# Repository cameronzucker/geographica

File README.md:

<!-- HEADER -->

# Geographica

**Offline-first GIS platform for field operations on disconnected networks.** A complete mapping stack — vector basemaps, aerial imagery, terrain, routing, geocoding, GPS — running on a single Raspberry Pi 5.

<br clear="left" />

<!-- ONE-PARAGRAPH ELABORATION -->
Built for [AREDN](https://www.arednmesh.org/) mesh networks and field teams operating without cloud connectivity. Acquire data once on a connected workstation, then deploy anywhere — wilderness, disaster recovery, off-grid bases, or mesh-network coverage areas. After initial data acquisition, no internet connection is required.

<!-- HERO SCREENSHOT -->

<!-- HOW IT WAS BUILT CALLOUT -->
> **How it was built:** 19 days. One engineer plus a team of Claude agents working under structured agent-orchestration patterns — brainstorm, adversarial review, TDD execution by parallel sub-agents. Inference cost: **~$300 of API-equivalent model output**, paid as a Claude Max subscription (~$200/mo). [Read the process →](docs/PROCESS.md) · [Cost methodology →](docs/COST_METHODOLOGY.md)

## Features

<p align="center">

<br>
<em>3D hillshade terrain (above) and public lands overlay with agency-colored fills (below).</em>
</p>

### Mapping & imagery

- **Vector basemaps** — three themes (Positron light, Dark Matter dark, Hybrid imagery+roads) with house-number labels.
- **Aerial imagery** — five acquisition modes (USGS Direct, NOAA NAIP, National Map ImageServer, USGS M2M API, BYO GeoTIFF). Per-source toggles, opacity slider, dynamic basemap restyling when imagery is active.
- **Public lands layer** — BLM, National Forest, National Park, Fish & Wildlife, Military, Bureau of Reclamation, Tribal, State Trust, and Wilderness boundaries. Agency-colored fills, tribal-boundary diagonal stripes, full legend.
- **3D terrain** — hillshade overlay, adjustable exaggeration slider, free-look camera (pitch/bearing control).

<br clear="right" />

### Spatial intelligence

- **Natural-language spatial search** — "nearest gas station", "hospitals near me", "gas stations along my route", "fuel every 50 miles", "gas stations in Flagstaff", "restaurants in Phoenix along my route". Distance-ranked results, numbered map pins, city-aware geocoding.
- **Voice search** — push-to-hold mic button for hands-free queries via Whisper (base.en, CPU). Requires HTTPS.
- **OSM POI search** — commercial amenities (fuel, food, lodging, pharmacy, grocery) and public-land boundaries extracted from OSM data.
- **Geocoding** — Nominatim-backed search for addresses, cities, landmarks.
- **POI search** — GNIS gazetteer with full-text search.

<br clear="right" />

### Navigation & GPS

- **Turn-by-turn navigation** — voice guidance, off-route detection, dead reckoning.
- **Multi-stop waypoint routing** — map-click point selection for car, bicycle, and pedestrian profiles.
- **Live GPS** — hardware GPS streaming over WebSocket with accuracy circle display.
- **KML/KMZ import** — drag-and-drop file overlay with layer management panel and IndexedDB session persistence.
- **Coordinate display** — Maidenhead grid locator and MGRS in addition to lat/lon.
- **Imperial and metric units** — switchable distance/elevation units.
- **Print/export directions** — Mapquest-style printable page.

<br clear="right" />

### Operations & admin

- **Admin config panel** (localhost-only, separated from main app) — 4-tab layout with Dashboard (service health, disk/TLS info), Pipelines (7-source card grid with MapLibre minimap bbox selection), Inventory (imagery coverage map with clustered markers), Settings (credential keyring, TLS config, STT status).
- **Pipeline management** — start/cancel imagery (5 modes), elevation, public lands, and OSM POI extraction from the browser, with phase-aware progress tracking and quad-level deduplication.
- **ATAK integration** — serves as a WMS map source for TAK clients.
- **TLS support** — three modes (HTTP, HTTPS self-signed, Tailscale Let's Encrypt).
- **Credential security** — API keys stored in GNOME Keyring via host-side daemon, shared with containers over tmpfs (no plaintext credential files).
- **No build step** — vanilla JS + MapLibre GL JS frontend, no bundler required.

<br clear="right" />

## Architecture

```mermaid
flowchart LR
    Browser["🌐 Browser"]
    NGINX["NGINX :8093"]
    NGINX_CFG["NGINX :8097<br/>(localhost only)"]
    TS["TileServer GL :8090<br/>vector / raster / elevation tiles"]
    VAL["Valhalla :8094<br/>routing engine"]
    NOM["Nominatim :8092<br/>geocoding (PostgreSQL)"]
    SRCH["Search :8096<br/>spatial search + admin API"]
    STT["STT :8098<br/>Whisper speech-to-text"]
    GPS["GPS :8095<br/>WebSocket GPS relay"]
    PIPE["Pipeline (on-demand)<br/>imagery / elevation / OSM POIs"]

    Browser --> NGINX
    NGINX --> TS
    NGINX --> VAL
    NGINX --> NOM
    NGINX --> SRCH
    NGINX --> STT
    NGINX --> GPS

    NGINX_CFG --> SRCH
    NGINX_CFG --> TS

    SRCH -.->|triggers| PIPE
    PIPE -.->|writes tiles| TS
```

Seven persistent Docker Compose services plus an on-demand pipeline container, with per-container memory limits to prevent OOM on constrained hardware. NGINX reverse-proxies all services behind a single port with URL rewriting for TileServer GL style/TileJSON endpoints. The configuration NGINX (port 8097) is bound to localhost only and serves the admin panel + pipeline-management API; the main NGINX (port 8093) serves the user-facing app.

The on-demand pipeline container runs imagery acquisition, elevation tile downloads, and OSM POI extraction. It writes new tiles into the data volume, and TileServer GL hot-reloads its config to pick them up without a restart.

## Hardware requirements

| Component | Minimum | Recommended |
|-----------|---------|-------------|
| Board | Raspberry Pi 5, 8 GB | Raspberry Pi 5, 16 GB |
| Storage | 256 GB SSD (single-state coverage) | 1 TB SSD (multi-state coverage) |
| GPS | — | Any gpsd-compatible receiver: Waveshare LC29H HAT, USB GPS dongle (u-blox, BU-353S4), etc. |
| NPU | — | Hailo 10H (for future NPU-accelerated STT) |

**Tested on:** Pi 5 16 GB, Debian Trixie (bookworm also works), Intel D3-S4610
896 GB SATA SSD.

**Storage budget** (Western US, 11 states):

| Dataset | Size |
|---------|------|
| Vector basemap (OpenMapTiles via Planetiler) | ~2.4 GB |
| Elevation tiles (zoom 0-14) | ~70-120 GB |
| Aerial imagery — scraper z0-z14 (USGS tile cache) | ~25 GB |
| Aerial imagery — NAIP z17 (NOAA, per region) | ~10-50 GB |
| Public lands (PAD-US + Census AIANNH tribal) | ~0.4 GB |
| OSM extracts (merged PBF) | ~3.1 GB |
| Valhalla routing graph | ~4.3 GB |
| Nominatim geocoding DB | ~30-40 GB |
| POI index (GNIS + OSM) | ~80 MB |
| **Total** | **~145-320 GB** |

Imagery size varies by region. z0-z14 scraper covers the full region at ~25 GB.
NOAA NAIP imagery is ~21 MB per NAIP quad after JPEG compression, edge erosion,
and inpainting. Northern Arizona (494 quads) is ~10 GB; all of Arizona (~2,000
quads) would be ~42 GB. The 3-stage pipeline processes ~0.7 tiles/min on a Pi 5
(~1.5 min/tile) — a full state takes 12-48 hours depending on quad count. Staging
requires ~4 GB temporary (8 concurrent 486 MB GeoTIFF downloads). Re-running with
a larger overlapping bbox skips already-processed quads automatically.

POI index includes GNIS geographic features + OSM commercial amenities + public land boundaries.

## Get started

For a guided setup experience, use the wizard:

```bash
git clone https://github.com/cameronzucker/geographica.git
cd geographica
sudo ./bootstrap.sh    # install system prerequisites
# log out and back in so the docker group takes effect, then:
./setup.sh             # launch browser-based setup wizard
```

Then open http://localhost:8099 to walk the wizard.

For step-by-step setup → [docs/SETUP.md](docs/SETUP.md)
For manual / advanced setup → [docs/MANUAL_SETUP.md](docs/MANUAL_SETUP.md)

## Project layout

```
geographica/
├── docker-compose.yml     # 7 persistent services + on-demand pipeline
├── services/              # GPS, search, STT (FastAPI services)
├── scripts/               # offline data pipeline (imagery, elevation, POIs)
├── frontend/              # vanilla JS + MapLibre GL JS app
├── nginx/                 # reverse-proxy config
├── tileserver/            # TileServer GL config and styles
├── setup/                 # browser-based setup wizard
├── docs/                  # SETUP.md, MANUAL_SETUP.md, PROCESS.md, COST_METHODOLOGY.md
├── bootstrap.sh           # system prerequisites (sudo)
├── setup.sh               # wizard launcher
└── data → /srv/geographica/data/   # symlink (gitignored): MBTiles, PBF, SQLite
```

## Further reading

- [docs/SETUP.md](docs/SETUP.md) — guided wizard install (5 minutes)
- [docs/MANUAL_SETUP.md](docs/MANUAL_SETUP.md) — manual install + advanced configuration
- [docs/PROCESS.md](docs/PROCESS.md) — how this was built with an AI agent team
- [docs/COST_METHODOLOGY.md](docs/COST_METHODOLOGY.md) — cost audit + reproduction
- [CHANGELOG.md](CHANGELOG.md) — release history
- [CONTRIBUTING.md](CONTRIBUTING.md) — commit conventions and PR flow
- [VERSIONING.md](VERSIONING.md) — versioning policy and hotfix recipe
- [UPGRADING.md](UPGRADING.md) — version-to-version migration notes

## License

MIT — see [LICENSE](LICENSE).

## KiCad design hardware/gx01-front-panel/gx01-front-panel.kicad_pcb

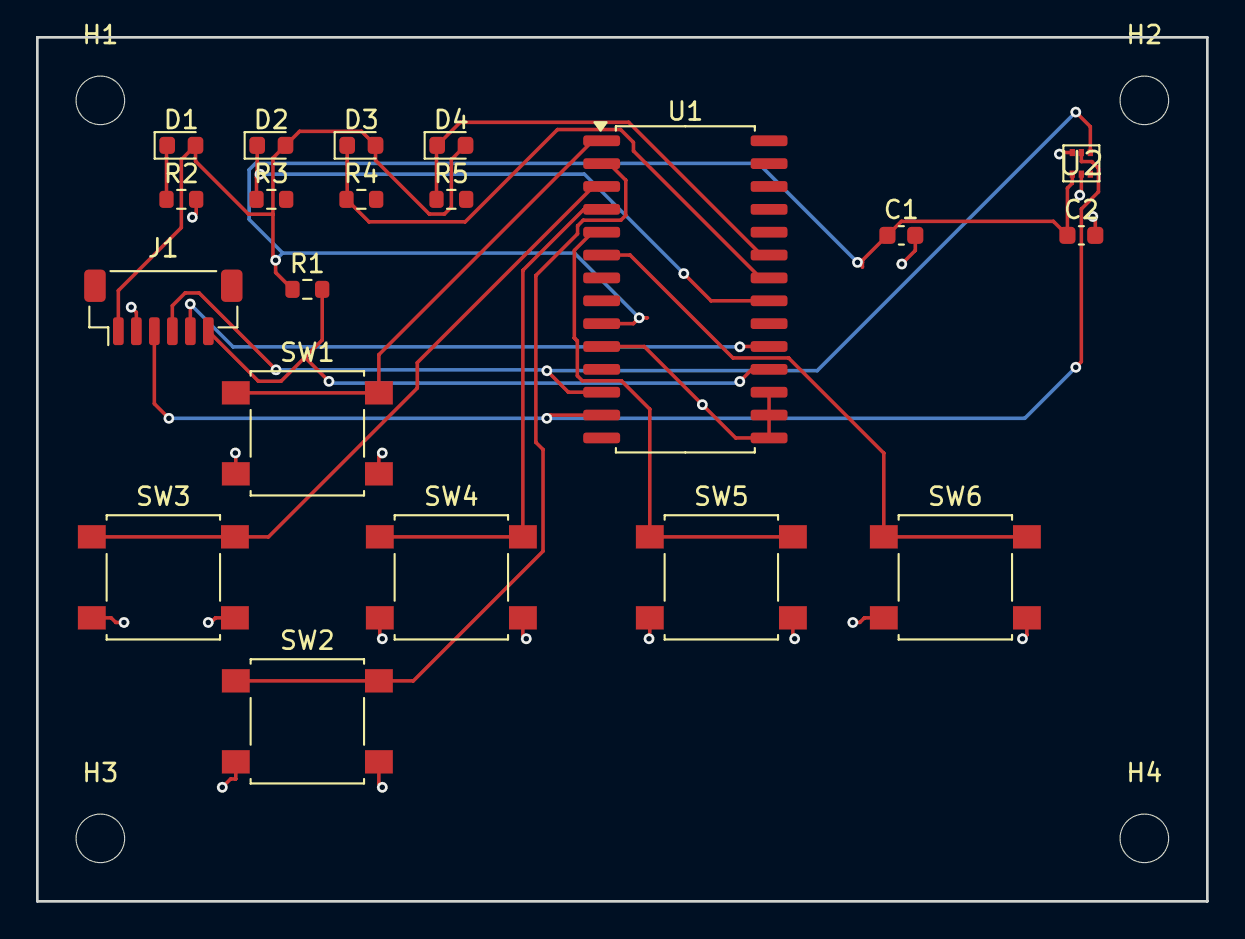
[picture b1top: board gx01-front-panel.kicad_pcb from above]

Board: 2 copper layers, 65.0 x 48.0 mm, 24 parts (0 on the bottom side), 16 nets.

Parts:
C1, C2: 100nF; C_0603_1608Metric
D1: PWR_Grn; LED_0603_1608Metric
D2: GPS_Blu; LED_0603_1608Metric
D3: NTP_Yel; LED_0603_1608Metric
D4: ERR_Red; LED_0603_1608Metric
H1, H2, H3, H4: MH_2.75; MountingHole_2.7mm_M2.5
J1: Cable; JST_SH_BM06B-SRSS-TB_1x06-1MP_P1.00mm_Vertical
R1: 10k; R_0603_1608Metric
R2, R3, R4, R5: 1k; R_0603_1608Metric
SW1: UP; SW_SPST_B3S-1000
SW2: DOWN; SW_SPST_B3S-1000
SW3: LEFT; SW_SPST_B3S-1000
SW4: RIGHT; SW_SPST_B3S-1000
SW5: SELECT; SW_SPST_B3S-1000
SW6: BACK; SW_SPST_B3S-1000
U1: MCP23017; SOIC-28W_7.5x17.9mm_P1.27mm
U2: VEML7700; VEML7700_OPLGA-6

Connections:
+3V3: C1.1, C2.1, D1.2, D2.2, D3.2, D4.2, J1.1, R1.1, U1.9, U2.6
D2_K: D2.1, R3.1, U1.21
D3_K: D3.1, R4.1, U1.22
D4_K: D4.1, R5.1, U1.23
GND: C1.2, C2.2, J1.2, R2.2, SW1.2, SW2.2, SW3.2, SW4.2, SW5.2, SW6.2, U1.10, U1.15, U1.16, U1.17, U2.1, U2.5
MCP_INT: J1.5, U1.19
MCP_RST: J1.6, R1.2, U1.18
PWR_K: D1.1, R2.1
SCL1: J1.4, U1.12, U2.3
SDA1: J1.3, U1.13, U2.2
SW_BACK: SW6.1, U1.6
SW_DOWN: SW2.1, U1.2
SW_LEFT: SW3.1, U1.3
SW_RIGHT: SW4.1, U1.4
SW_SEL: SW5.1, U1.5
SW_UP: SW1.1, U1.1

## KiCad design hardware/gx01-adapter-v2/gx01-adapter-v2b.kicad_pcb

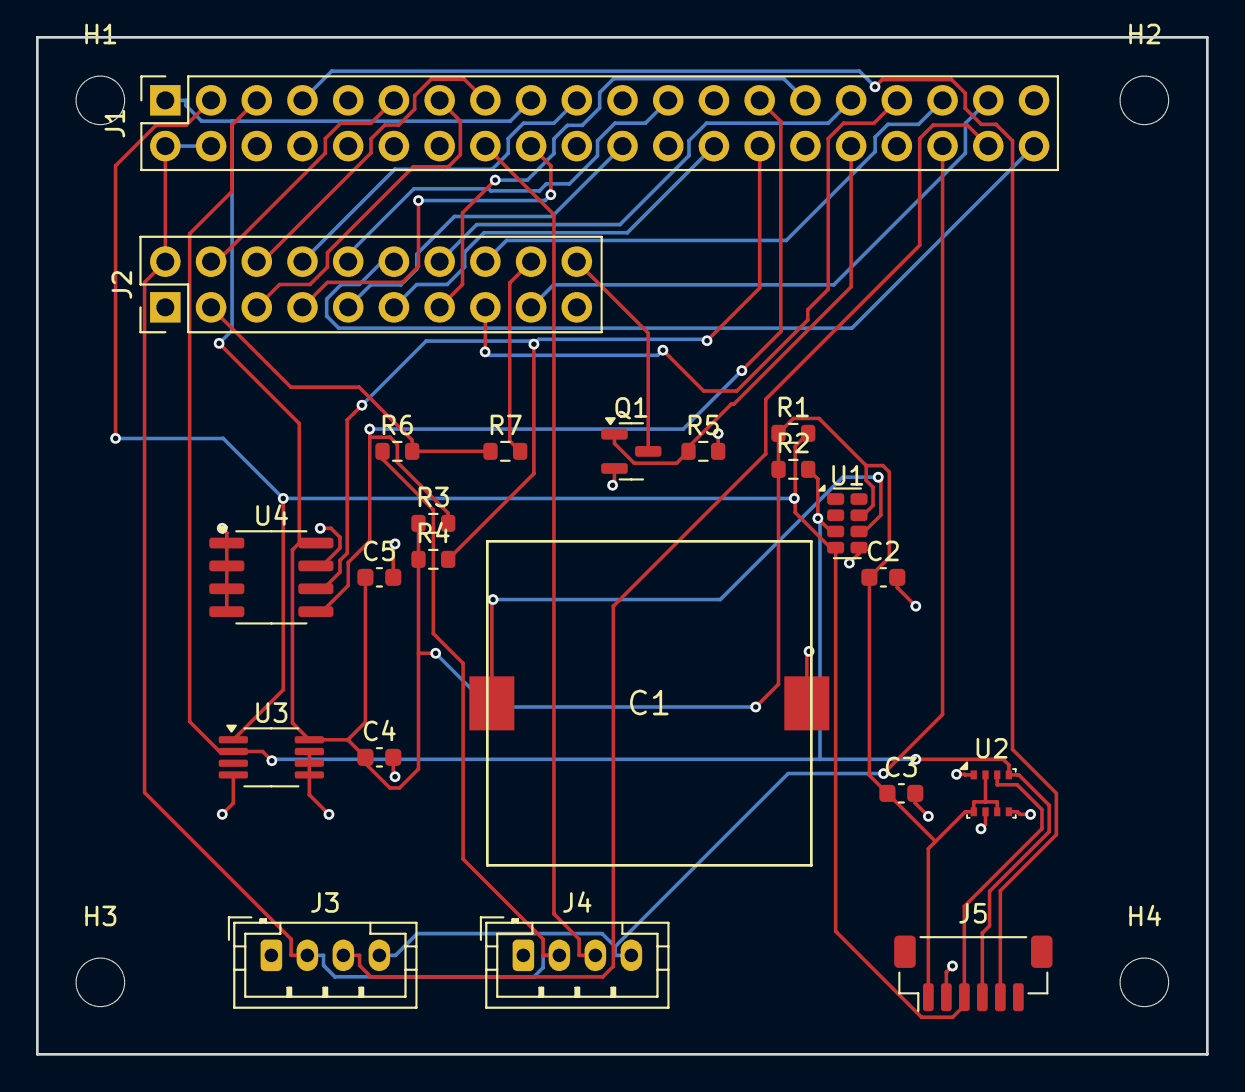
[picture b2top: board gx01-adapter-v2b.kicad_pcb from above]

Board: 2 copper layers, 65.0 x 56.5 mm, 26 parts (0 on the bottom side), 30 nets.

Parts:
C1: CR1632 holder; CR1632_Holder_SMT
C2, C3, C4, C5: 100nF; C_0603_1608Metric
H1, H2, H3, H4: MH_2.75; MountingHole_2.7mm_M2.5
J1: Pi GPIO 40-pin; PinSocket_2x20_P2.54mm_Vertical
J2: LCD 2x10 IDC; PinHeader_2x10_P2.54mm_Vertical
J3: Fan 1; JST_PH_B4B-PH-K_1x04_P2.00mm_Vertical
J4: Fan 2; JST_PH_B4B-PH-K_1x04_P2.00mm_Vertical
J5: FPB cable; JST_SH_BM06B-SRSS-TB_1x06-1MP_P1.00mm_Vertical
Q1: AO3400A; SOT-23
R1, R2: 4.7k; R_0603_1608Metric
R3, R4: 3.3k; R_0603_1608Metric
R5, R6, R7: 10k; R_0603_1608Metric
U1: RV-3028-C7; MicroCrystal_C7_SON-8_1.5x3.2mm_P0.9mm
U2: BME280; Bosch_LGA-8_2.5x2.5mm_P0.65mm_ClockwisePinNumbering
U3: MCP9808; MSOP-8_3x3mm_P0.65mm
U4: 24LC32; SOIC-8_3.9x4.9mm_P1.27mm

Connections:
+3V3: C2.1, C3.1, C4.1, C5.1, J1.1, J1.17, J5.1, R1.1, R2.1, R3.1, R4.1, U1.7, U2.2, U2.6, U2.8, U3.8, U4.8
+5V: J1.2, J1.4, J2.2, J3.2, J4.2, R6.1
BL_PWM: J1.32, Q1.1, R5.1
FAN1_TACH: J1.38, J3.3
FAN2_TACH: J1.16, J4.3
FAN_PWM: J1.36, J3.4, J4.4
FPB_INT: J1.7, J5.5
GND: C1.2, C2.2, C3.2, C4.2, C5.2, J1.6, J1.9, J1.14, J1.20, J1.25, J1.30, J1.34, J1.39, J2.1, J3.1, J4.1, J5.2, Q1.2, R5.2, U1.5, U2.1, U2.5, U2.7, U3.4, U3.5, U3.6, U3.7, U4.1, U4.2, U4.3, U4.4, U4.7
ID_SC: J1.28, R4.2, U4.6
ID_SD: J1.27, R3.2, U4.5
LCD_BLK: J2.20, Q1.3
LCD_CS1: J1.33, J2.15
LCD_CS2: J1.35, J2.16
LCD_DB0: J1.18, J2.7
LCD_DB1: J1.19, J2.8
LCD_DB2: J1.22, J2.9
LCD_DB3: J1.23, J2.10
LCD_DB4: J1.26, J2.11
LCD_DB5: J1.40, J2.12
LCD_DB6: J1.29, J2.13
LCD_DB7: J1.31, J2.14
LCD_E: J1.15, J2.6
LCD_RS: J1.11, J2.4
LCD_RST: J1.37, J2.17
LCD_RW: J1.13, J2.5
LCD_V0: J2.3, R6.2, R7.1
LCD_VEE: J2.18, R7.2
SCL1: J1.5, J5.4, R2.2, U1.3, U2.4, U3.2
SDA1: J1.3, J5.3, R1.2, U1.4, U2.3, U3.1
VBACKUP: C1.1, U1.6

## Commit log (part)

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2026-04-19 chore(main): release 1.3.2
2026-04-19 chore(main): release 1.3.3
2026-04-19 chore(main): release 1.4.0
2026-04-19 chore(main): release 1.5.0
2026-04-19 chore(main): release 1.5.1
2026-04-19 chore(main): release 1.5.2
2026-04-20 chore(main): release 1.5.3
2026-04-20 fix(setup): update stale STATE_BBOXES location in error message
    Post-extraction follow-up. STATE_BBOXES lives at
    scripts/common/state_bboxes.py now; the error pointed at the old
    setup/runner.py location.
2026-04-20 docs(noaa): log Phase 0 NAIP CONUS expansion progress
    Narrative entry capturing the in-progress work: spec v2 (post
    5-round adversarial review), plan, and Phase 0 (Tasks 1-2) commits.
    Tracks the notable findings from adversarial review (setup/runner.py
    not in pipeline container; B2/B3 misattribution; filter-always-runs
    wrong for TX/CA; disk model peak-vs-final).
    Phase 0 = 2/39 tasks complete on feat/noaa-conus branch.
2026-04-20 docs(noaa): update implementation log — Phase 1 complete, tile-index URL follow-up
2026-04-20 docs(start): point new sessions at NOAA CONUS handoff
    Phase 0+1 of the NOAA NAIP CONUS expansion are committed on the
    feat/noaa-conus worktree (10/39 tasks). Surface the in-flight work
    prominently so a fresh agent picking up the project sees the
    handoff doc before anything else.
    Handoff: memory/handoff_20260420_noaa_conus_phase1_complete.md
2026-04-20 feat(noaa): whole-state mode skips ogr2ogr filter
    Whole-state uses the full tile index directly (no -spat call) because
    the filter step's timeout couldn't handle TX/CA-sized shapefiles.
    Bbox mode gets a 300s timeout (was 60s).
    Closes adversarial review M2.
2026-04-20 feat(noaa): checkpoint PK = (snapshot, usps, filename)
    NAIP border quads are shipped in both states' directories. Old PK
    of tile_filename alone silently deduped the second state. New PK
    preserves per-state entries; merger is idempotent on tile coords.
    catalog_snapshot and state_usps default to '' so legacy callsite
    at line ~2497 (INSERT ... tile_filename only) continues to work
    during the progressive migration; Tasks 15/18 will replace that
2026-04-20 feat(noaa): POST /admin/pipeline/noaa/refresh endpoint
    Thin wrapper over refresh_catalog(). Returns 409 on lock conflict or
    active pipeline; 200 with status=truncated for Azure paginator issues.
2026-04-20 feat(noaa): POST /admin/pipeline/noaa/rollback endpoint
    Swaps the catalog symlink to a prior snapshot. 409 if any pipeline is
    running; 404 if the snapshot is missing. Logs the rollback to the
    refresh-log for audit.
    Closes adversarial review M10.
2026-04-20 feat(noaa): POST /admin/pipeline/noaa/force-unlock endpoint
    Removes the refresh lockfile only if the holder PID is no longer alive
    (see force_unlock helper). 409 if the holder is still running.
2026-04-20 feat(noaa): GET /admin/pipeline/noaa/refresh-log endpoint
    Returns the refresh history (JSONL log). Entries are reverse chronological.
    Each gets a rollback_available flag based on whether the snapshot file is
    still on disk (not pruned).
2026-04-20 feat(frontend): NOAA custom-area tab shows current bbox + prompts when empty
    The Custom area tab now reads #cfg-bbox.value live and renders either
    "Using bbox: -112.000, 35.100, -111.500, 35.400" (monospace, success
    color) or a yellow prompt asking the user to draw or paste a bbox.
    Updates on input, change, and tab-activation events.
    Note: no UI test infra exists for this component; test coverage deferred
    to Playwright when that suite is added.
2026-04-20 feat(frontend): NOAA estimate UI — peak-disk gate + acknowledge_missing + bbox validation
    Three UX guards wired into the estimate-box rendering and start handlers:
    - Peak-working-set disk: >85% shows yellow warning; >100% shows red
    block and disables Start (estBox._diskBlocked flag). Matches Spec §3.7.
    - Missing states: if d.missing[] is non-empty, the rendered checkbox
    now gates Start — unchecked triggers an explicit alert rather than
    silently sending acknowledge_missing=false and getting a 409. The
2026-04-20 feat(frontend): NOAA catalog refresh-history panel + rollback button
    Collapsible section under the NOAA card shows the most recent
    catalog-refresh log entries (reverse-chronological) with per-entry
    [Rollback] buttons when rollback_available is true. A "Refresh
    catalog now" button triggers /admin/pipeline/noaa/refresh and
    reloads the log on completion.
    No UI test infra exists for this component; manual verification
2026-04-20 feat(frontend): NOAA partial_failed pipeline — retry-failed-states UI
    When a NOAA pipeline finishes with status=partial_failed, the pipeline
    card surfaces the per_state breakdown and a "Retry failed state(s)"
    button that starts a new pipeline for the failed entries. MVP: the
    existing /admin/pipeline/start endpoint accepts ONE state per request,
    so multi-state retry is sequential (user clicks Retry, then clicks
    again for the next failed state). Passes acknowledge_missing=true on
2026-04-20 test(noaa): synthetic tile-index shapefile fixtures for Phase 5
    Two states with 10 footprints each (arizona_test.shp, utah_test.shp).
    One border-quad with filename "m_border.tif" appears in both — exercises
    the composite-PK checkpoint table's per-state dedup (Task 14). Helper
    script at tests/fixtures/build_test_shapefiles.py regenerates them.
    Agent: cairn
2026-04-20 test(noaa): complete Azure XML fixture set for pagination + edge cases
    Added: empty_container.xml (zero blobs), mixed_valid_invalid.xml
    (one real USPS + one unparseable directory name). Preserves the three
    existing fixtures from Task 4. Integration test in Task 35 exercises
    the full matrix.
    Agent: cairn
2026-04-20 test(noaa): Phase 5 integration — catalog refresh + resolver + queue
    Exercises refresh_catalog() end-to-end against mocked Azure (fixtures
    from Task 34) + synthetic shapefiles (Task 33). Regression guards:
    - tile-index URL pattern (the 4ffd658 fix)
    - border-quad composite-PK checkpoint (Task 14)
    - resolver split into candidates + missing (Task 11)
    - unified queue tuple shape (Task 13)
2026-04-26 chore(main): release 2.0.0
